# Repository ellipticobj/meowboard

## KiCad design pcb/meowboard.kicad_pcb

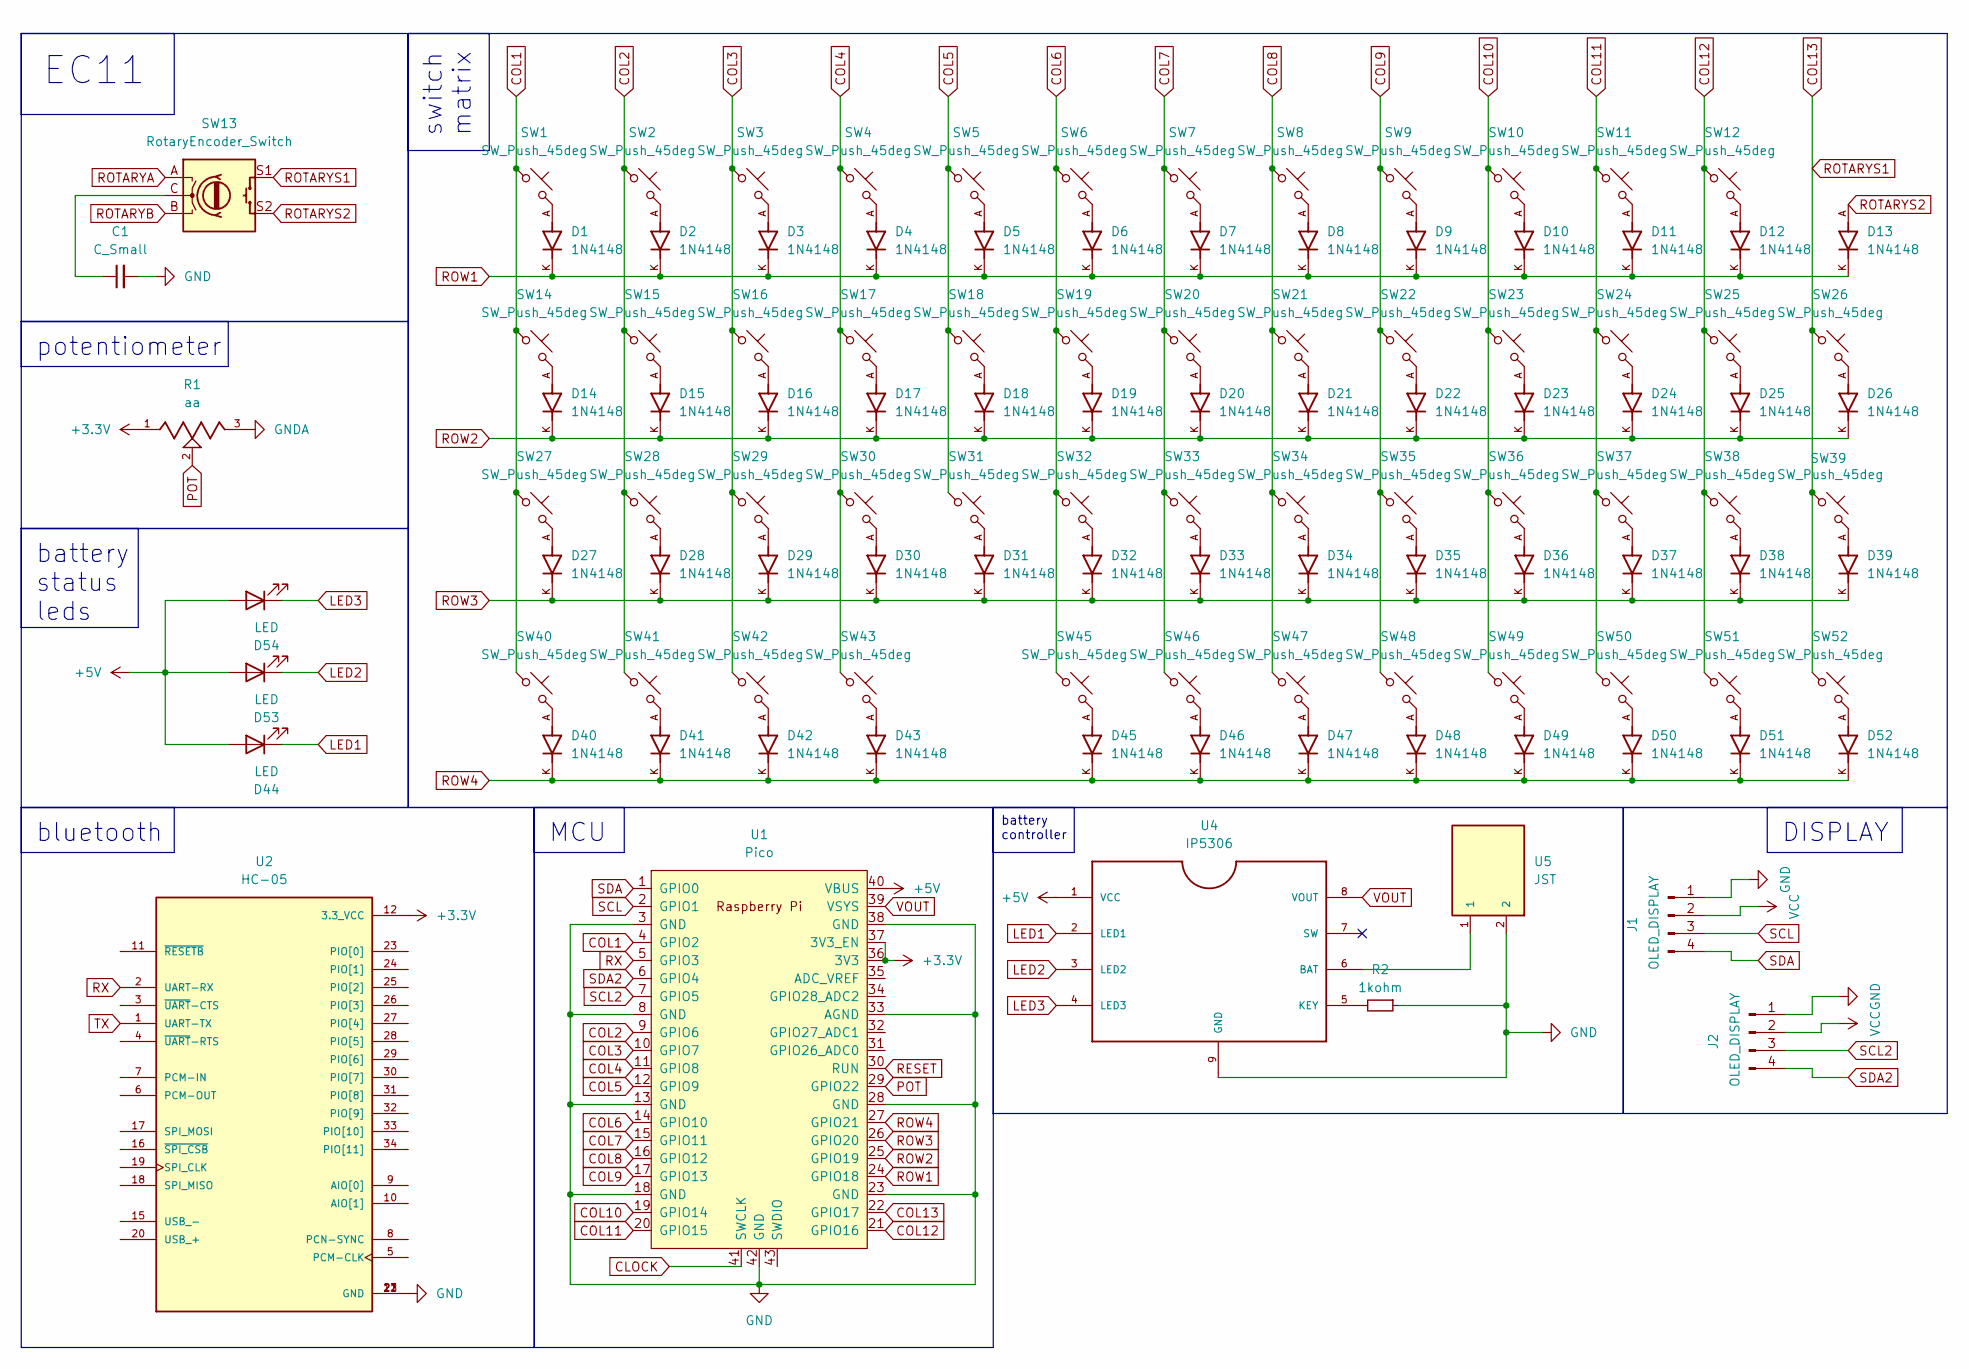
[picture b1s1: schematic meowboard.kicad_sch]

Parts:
C1: C_Small; CP_Radial_D4.0mm_P1.50mm
D1, D2, D3, D4, D5, D6, D7, D8, D9, D10, D11, D12, D13, D14, D15, D16, D17, D18, D19, D20, D21, D22, D23, D24, D25, D26, D27, D28, D29, D30, D31, D32, D33, D34, D35, D36, D37, D38, D39, D40, D41, D42, D43, D45, D46, D47, D48, D49, D50, D51, D52: 1N4148; DIOAD753W49L380D172B; PARTREV 5
D44, D53, D54: LED; LED_D1.8mm_W1.8mm_H2.4mm_Horizontal_O1.27mm_Z1.6mm
J1, J2: OLED_DISPLAY; SSD1306-0.91-OLED-4pin-128x32
R1: aa; TRIM_3310Y-001-103L
R2: 1kohm; R_Axial_DIN0204_L3.6mm_D1.6mm_P1.90mm_Vertical
SW1, SW2, SW3, SW4, SW5, SW6, SW7, SW8, SW9, SW10, SW11, SW14, SW15, SW16, SW17, SW18, SW19, SW20, SW21, SW22, SW23, SW24, SW25, SW26, SW27, SW28, SW29, SW30, SW31, SW32, SW33, SW34, SW35, SW36, SW37, SW38, SW39, SW40, SW41, SW42, SW45, SW46, SW47, SW48, SW49, SW50, SW51, SW52: SW_Push_45deg; MX-Hotswap-1U
SW12, SW43: SW_Push_45deg; MX-Hotswap-2U
SW13: RotaryEncoder_Switch; RotaryEncoder_Alps_EC11E-Switch_Vertical_H20mm
U1: Pico; RPi_Pico_SMD_TH
U2: HC-05; XCVR_HC-05; PARTREV v1.0
U4: IP5306; SOIC9P127_490X600X170L84X42T330X241N
U5: JST; SM4-CON

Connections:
+3.3V: R1.1, U1.36 (3V3), U1.37 (3V3_EN), U2.12 (3.3_VCC)
+5V: D44.2 (A), D53.2 (A), D54.2 (A), U1.40 (VBUS), U4.1 (VCC)
CLOCK: U1.41 (SWCLK)
COL1: SW1.1, SW14.1, SW27.1, SW40.1, U1.4 (GPIO2)
COL2: SW2.1, SW15.1, SW28.1, SW41.1, U1.9 (GPIO6)
COL3: SW3.1, SW16.1, SW29.1, SW42.1, U1.10 (GPIO7)
COL4: SW4.1, SW17.1, SW30.1, SW43.1, U1.11 (GPIO8)
COL5: SW5.1, SW18.1, SW31.1, U1.12 (GPIO9)
COL6: SW6.1, SW19.1, SW32.1, SW45.1, U1.14 (GPIO10)
COL7: SW7.1, SW20.1, SW33.1, SW46.1, U1.15 (GPIO11)
COL8: SW8.1, SW21.1, SW34.1, SW47.1, U1.16 (GPIO12)
COL9: SW9.1, SW22.1, SW35.1, SW48.1, U1.17 (GPIO13)
COL10: SW10.1, SW23.1, SW36.1, SW49.1, U1.19 (GPIO14)
COL11: SW11.1, SW24.1, SW37.1, SW50.1, U1.20 (GPIO15)
COL12: SW12.1, SW25.1, SW38.1, SW51.1, U1.21 (GPIO16)
COL13: SW13.S1, SW26.1, SW39.1, SW52.1, U1.22 (GPIO17)
GND: C1.2, J1.1, J2.1, R2.1, U1.3 (GND), U1.8 (GND), U1.13 (GND), U1.18 (GND), U1.23 (GND), U1.28 (GND), U1.33 (AGND), U1.38 (GND), U1.42 (GND), U2.13 (GND), U2.21 (GND), U2.22 (GND), U4.9 (GND), U5.2
GNDA: R1.3
LED1: D44.1 (K), U4.2 (LED1)
LED2: D53.1 (K), U4.3 (LED2)
LED3: D54.1 (K), U4.4 (LED3)
unnamed: C1.1, SW13.C
unnamed: D1.A, SW1.2
unnamed: D2.A, SW2.2
unnamed: D3.A, SW3.2
unnamed: D4.A, SW4.2
unnamed: D5.A, SW5.2
unnamed: D6.A, SW6.2
unnamed: D7.A, SW7.2
unnamed: D8.A, SW8.2
unnamed: D9.A, SW9.2
unnamed: D10.A, SW10.2
unnamed: D11.A, SW11.2
unnamed: D12.A, SW12.2
unnamed: D14.A, SW14.2
unnamed: D15.A, SW15.2
unnamed: D16.A, SW16.2
unnamed: D17.A, SW17.2
unnamed: D18.A, SW18.2
unnamed: D19.A, SW19.2
unnamed: D20.A, SW20.2
unnamed: D21.A, SW21.2
unnamed: D22.A, SW22.2
unnamed: D23.A, SW23.2
unnamed: D24.A, SW24.2
unnamed: D25.A, SW25.2
unnamed: D26.A, SW26.2
unnamed: D27.A, SW27.2
unnamed: D28.A, SW28.2
unnamed: D29.A, SW29.2
unnamed: D30.A, SW30.2
unnamed: D31.A, SW31.2
unnamed: D32.A, SW32.2
unnamed: D33.A, SW33.2
unnamed: D34.A, SW34.2
unnamed: D35.A, SW35.2
unnamed: D36.A, SW36.2
unnamed: D37.A, SW37.2
unnamed: D38.A, SW38.2
unnamed: D39.A, SW39.2
unnamed: D40.A, SW40.2
unnamed: D41.A, SW41.2
unnamed: D42.A, SW42.2
unnamed: D43.A, SW43.2
unnamed: D45.A, SW45.2
unnamed: D46.A, SW46.2
unnamed: D47.A, SW47.2
unnamed: D48.A, SW48.2
unnamed: D49.A, SW49.2
unnamed: D50.A, SW50.2
unnamed: D51.A, SW51.2
unnamed: D52.A, SW52.2
unnamed: U4.6 (BAT), U5.1
unnamed: R2.2, U4.5 (KEY)
POT: R1.2, U1.29 (GPIO22)
RESET: U1.30 (RUN)
ROTARYA: SW13.A
ROTARYB: SW13.B
ROTARYS2: D13.A, SW13.S2
ROW1: D1.K, D2.K, D3.K, D4.K, D5.K, D6.K, D7.K, D8.K, D9.K, D10.K, D11.K, D12.K, D13.K, U1.24 (GPIO18)
ROW2: D14.K, D15.K, D16.K, D17.K, D18.K, D19.K, D20.K, D21.K, D22.K, D23.K, D24.K, D25.K, D26.K, U1.25 (GPIO19)
ROW3: D27.K, D28.K, D29.K, D30.K, D31.K, D32.K, D33.K, D34.K, D35.K, D36.K, D37.K, D38.K, D39.K, U1.26 (GPIO20)
ROW4: D40.K, D41.K, D42.K, D43.K, D45.K, D46.K, D47.K, D48.K, D49.K, D50.K, D51.K, D52.K, U1.27 (GPIO21)
RX: U1.5 (GPIO3), U2.2 (UART-RX)
SCL: J1.3, U1.2 (GPIO1)
SCL2: J2.3, U1.7 (GPIO5)
SDA: J1.4, U1.1 (GPIO0)
SDA2: J2.4, U1.6 (GPIO4)
TX: U2.1 (UART-TX)
VCC: J1.2, J2.2
VOUT: U1.39 (VSYS), U4.8 (VOUT)

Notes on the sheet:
DISPLAY
potentiometer
MCU
EC11
bluetooth
battery status leds
battery controller
switch matrix

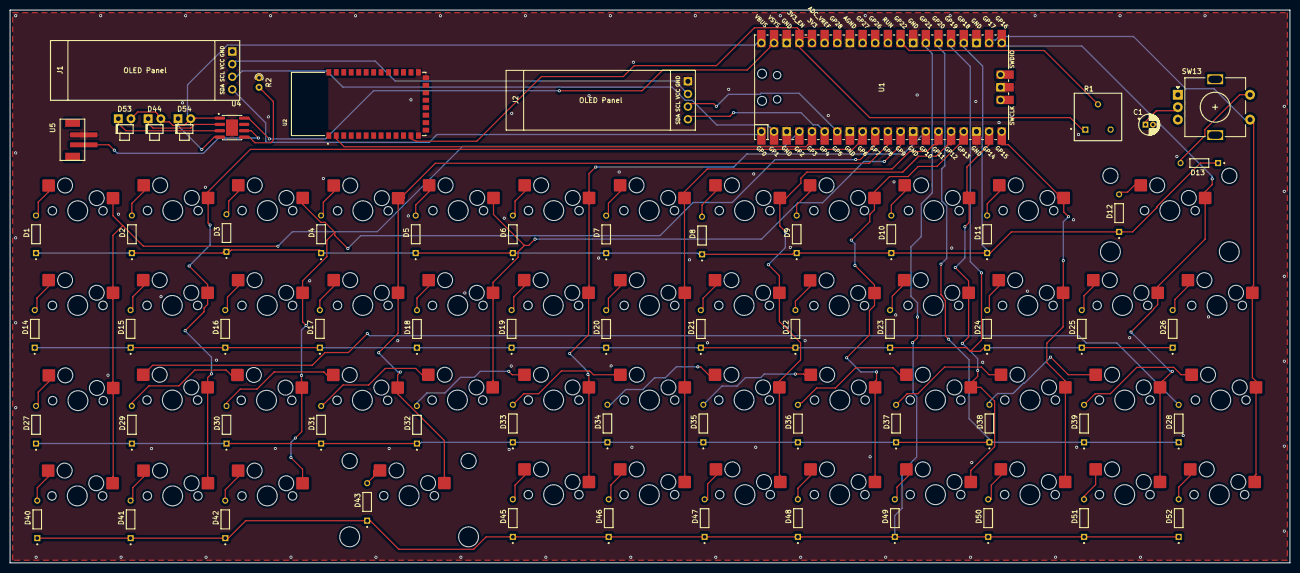
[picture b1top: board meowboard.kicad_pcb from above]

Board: 2 copper layers, 257.0 x 111.0 mm, 114 parts (0 on the bottom side), 85 nets.

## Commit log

2025-02-17 upload
2025-04-30 real
